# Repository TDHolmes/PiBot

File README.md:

# PiBot

MicroPython based robot designed for openness, flexibility, and education.

## Design
The PiBot is designed for simplicity, but also expandability. It is based on MicroPython at its core
and features simple to use pre-made APIs to interface with the hardware, allowing for easy design of
your robot.

## Hardware
The PiBot uses:
 - a mk20dx256vlh7 processor, just like the teensy 3.1 and 3.2
 - a MC33926PNB motor driver
 - pololu motors + encoders (for beta unit)

TESTING SHIT

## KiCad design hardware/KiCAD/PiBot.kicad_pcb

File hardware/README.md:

# Hardware
This folder will contain all PCB and schematic files written in KiCad

# Schematic Symbol Design Specs
* Name Text Size: 0.635mm
* Number Text Size: 0.635mm
* Length: 2.54mm

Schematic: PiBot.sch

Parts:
C1: 100uF; C_1210
C2, C7, C8: 10uF; C_1206
C3, C6: 1uF; C_0402
C4: 10nF; C_0402
C5: 0.1uF; C_0402
D1, D2, D4, D6: LED; PLCC2-LED-Reverse; Part Number XZVG45S-9
D3: Schottky; SOD-323; MPN CUS10S30H3FCT-ND
D5: 5.1V; SMA_Standard; Part Number SMAZ5V1-13-F
D7: 3.3V; SOD-323; Part Number MM3Z3V3ST1G
JP1, JP2: Jumper_NC_Small; Jumper-NC
JP3: Jumper_NO_Small; Jumper-NO
P2: CONN_02X05; Pin_Header_Straight_2x05_Pitch1.27mm
P3: I2C_EXPANSION; Pin_Header_Straight_2x01_Pitch2.54mm
P5: Feather-Adaper; feather-headers
PTC1: 0.5A; Fuse_SMD1206_Reflow; MPN 0ZCJ0050FF2G
R1: 150R; R_0402
R2, R6: 62R; R_0402
R3: 200R; R_0805
R4, R5, R7, R8, R10: 10k; R_0402
R9: 15k; R_0402
SD1: SD_CARD_SLOT_MICRO_RIGHT; MF_Connectors-MF-MICROSD
TP1, TP2, TP3, TP5, TP7, TP8, TP9, TP11, TP13, TP14, TP15, TP17, TP19, TP21, TP23, TP25, TP27, TP29, TP31, TP33, TP35, TP37, TP39, TP41, TP43, TP45, TP47, TP49: TEST; Measurement_Point_Round-SMD-Pad_Small
U1: DMG2302U; SOT-23
U2: MKL03ZxxVFK4; QFN-24_4x4mm_Pitch0.5mm

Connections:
+3V3: C1.1, C2.1, C3.1, C4.1, C5.1, C6.1, C7.1, JP2.1, P2.1, P5.27, R2.1, R4.1, R5.1, R6.1, R7.1, SD1.PIN4, TP1.1, U2.3; also elsewhere on the board
+5V: PTC1.1, R1.1, TP7.1; also elsewhere on the board
+BATT: R3.1, R9.2, TP13.1; also elsewhere on the board
/F_VBUS: D3.1, D5.1, P5.3
/I2C_LSB_BIT: JP2.2, JP3.2, U2.21
/VBATT_MONITOR: C8.1, D7.1, R9.1, R10.2, U2.16
FB_L: TP49.1, U2.15; also elsewhere on the board
FB_R: TP29.1, U2.12; also elsewhere on the board
GND: C1.2, C2.2, C3.2, C4.2, C5.2, C6.2, C7.2, C8.2, D1.1, D2.1, D4.1, D5.2, D7.2, JP3.1, P2.3, P2.5, P2.9, P5.13, P5.25, R8.1, R10.1, SD1.G0, SD1.G1, SD1.PIN6, TP2.1, TP8.1, TP14.1, U1.2, U2.4; also elsewhere on the board
MISO: P5.16, SD1.PIN7, TP33.1
MOSI: P5.17, SD1.PIN3, TP31.1
MotorL_Inv: TP45.1, U2.10; also elsewhere on the board
Motor_In1: TP9.1, U2.5; also elsewhere on the board
Motor_In2: TP11.1, U2.6; also elsewhere on the board
unnamed: D1.2, R1.2
unnamed: D2.2, R2.2
unnamed: D3.2, PTC1.2
unnamed: D4.2, R3.2
unnamed: D6.1, U1.3
unnamed: D6.2, R6.2
unnamed: JP1.1, P5.19
unnamed: SD1.PIN1, SD1.PIN9
PG: P5.2, TP3.1; also elsewhere on the board
RESET: P2.10, U2.23
SCK: P5.18, SD1.PIN5, TP27.1
SCL: P3.1, P5.11, R5.2, TP17.1, U2.17; also elsewhere on the board
SDA: P3.2, P5.12, R4.2, TP21.1, U2.18; also elsewhere on the board
SD_CS: JP1.2, R8.2, SD1.PIN2, TP37.1
SWCLK: P2.4, U2.22
SWDIO: P2.2, U2.24
SWO: P2.6, U2.19
front_bumper: TP47.1, U2.11; also elsewhere on the board
left_encA: TP35.1, U2.1; also elsewhere on the board
left_encB: TP39.1, U2.2; also elsewhere on the board
rear_bumper: TP43.1, U2.8; also elsewhere on the board
right_encA: TP15.1, U2.13; also elsewhere on the board
right_encB: TP19.1, U2.14; also elsewhere on the board
~MotorL_D: TP41.1, U2.9; also elsewhere on the board
~MotorR_D: TP23.1, U2.20; also elsewhere on the board
~MotorSF: TP5.1, U1.1, U2.7; also elsewhere on the board
~RST: P5.28, R7.2

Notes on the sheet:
PycoBot (Teensy uPython Robot)
By: Broderick Carlin Tyler Holmes
MIT License
5v Line Up
On Feather boards, VBUS connects directly to USB power. This is protection circuitry so we don’t blow our computers (or the feather circuitry).
Enable proc if our 5v line is up
5v line cannot be back-fed from proc.
Blinkies
Optionally, tie SD CS line low perminantly
3v3 Line Up
BATT Line Up
PTA5 - TPM0_CH1 SPI0_SS_b PTA6 - TPM0_CH0 SPI0_MISO PTB10 - TPM0_CH1 SPI0_SS_b PTB11 - TPM0_CH0 SPI0_MISO PTB5 - TPM1_CH1 CMP0_IN1 PTA12 - TPM1_CH0 TPM_CLKIN0
PWM Pins
Sensors
Power
*All LED's PN: XZVG45S-9
Motors
Debug + Expansion
SD Card
2.5:1 voltage divider
Motors OK
Test Points

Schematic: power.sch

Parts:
BT1, BT2, BT3, BT4: Battery; AA_Batt; Part Number BK-92
C9, C10, C13: 0.1uF; C_0402
C11, C12: 10uF; C_1206
C14: 10pf; C_0402
C15, C16, C17: 22uf; R_0402
D8, D9: 5.1V; SMA_Standard; Part Number SMAZ5V1-13-F
D10: 7.5V; SOD-323; Part Number DZ2J075M0L
JP4, JP18: Jumper_NO_Small; Jumper-NO
JP17: Jumper_NC_Small; NetTie-I_Connected_SMD
L1: 1 uH; Neosid_Inductor_SM-NE29_SMD1008; Part Number SRN2512-1R0M
R11, R12, R16: 0; R_0805
R13, R14: 1M; R_0402
R15: 111k; R_0402
R32: 10k; R_0402
SW1: SPST; JS202011SCQN; Part Number JS202011SCQN
U3, U17: N-FET; SOT-23; Part Number DMG2302U
U4: TPS63060; DFN-10-w_pad

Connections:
+5V: R16.2; also elsewhere on the board
+BATT: C11.1, C12.1, R11.2, U4.2, U4.3; also elsewhere on the board
/power/BATT_GND_TERM: BT4.2, D9.1, JP18.1, R32.2, U17.2
/power/BATT_V+_TERM: BT1.1, C9.1, C10.1, D8.1, D10.1, R11.1, SW1.2, U3.1
/power/PSU_FB: C14.1, R14.2, R15.1, U4.8
/power/PSU_IND: L1.1, U4.1
/power/PSU_VOUT: C15.1, C16.1, C17.1, R13.1, R14.1, R16.1, U4.9
GND: C10.2, C11.2, C12.2, C13.2, C14.2, C15.2, C16.2, C17.2, D10.2, JP4.2, JP17.1, R15.2, U3.2, U4.4, U4.7, U4.PAD; also elsewhere on the board
GNDPWR: JP17.2; also elsewhere on the board
unnamed: BT1.2, BT2.1
unnamed: BT2.2, BT3.1
unnamed: BT3.2, BT4.1
unnamed: C9.2, JP4.1, JP18.2, U3.3, U17.3
unnamed: C13.1, U4.6
unnamed: D8.2, D9.2
unnamed: L1.2, U4.10
unnamed: R12.2, R13.2, U4.5
unnamed: R32.1, SW1.1, U17.1
PG: R12.1; also elsewhere on the board

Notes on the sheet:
PycoBot (Teensy uPython Robot)
By: Broderick Carlin Tyler Holmes
MIT License

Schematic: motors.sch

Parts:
C18, C19, C22, C23, C24, C25, C26, C27, C28, C29, C30, C31: 0.1uF; C_0402
C20, C21, C32, C33: 1uF; C_0402
C34, C35: 10uF; C_1206
D11, D12: 3.3V; SOD-323; Part Number MM3Z3V3ST1G
JP5, JP6, JP11, JP12, JP13, JP14: Jumper_NC_Small; Jumper-NC
JP7, JP8, JP9, JP10: Jumper_NO_Small; Jumper-NO
R17, R18: 200; R_0805
R19, R20: 100; R_0402
R21, R22, R23, R24, R25, R26, R27: 10k; R_0402
U5, U6: MC33926PNB; PQFN-32-EP-0.8mm
U7, U8: Motor; Sanyo_GearMotor
U9, U10, U11, U12: AH3772; SOT-23

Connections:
+3V3: C24.1, C25.1, C26.1, C27.1, C30.1, C31.1, R23.1, R24.1, R25.1, R26.1, R27.1, U7.3, U8.3, U9.1, U10.1, U11.1, U12.1; also elsewhere on the board
+BATT: C18.1, C19.1, C28.1, C29.1, C32.1, C33.1, C34.1, C35.1, U5.4, U5.6, U5.11, U5.31, U6.4, U6.6, U6.11, U6.31; also elsewhere on the board
FB_L: JP5.1; also elsewhere on the board
FB_R: JP6.1; also elsewhere on the board
GND: C20.2, C21.2, C24.2, C25.2, C26.2, C27.2, C30.2, C31.2, D11.2, D12.2, R17.2, R18.2, R21.2, R22.2, U5.5, U5.pad, U6.5, U6.pad, U7.6, U8.6, U9.2, U10.2, U11.2, U12.2; also elsewhere on the board
GNDPWR: C28.2, C29.2, C32.2, C33.2, C34.2, C35.2, U5.18, U5.19, U5.20, U5.22, U5.23, U5.24, U6.18, U6.19, U6.20, U6.22, U6.23, U6.24; also elsewhere on the board
MotorL_Inv: U5.7; also elsewhere on the board
Motor_In1: U5.2, U6.2; also elsewhere on the board
Motor_In2: U5.1, U6.1; also elsewhere on the board
unnamed: C18.2, U6.32
unnamed: C19.2, U5.32
unnamed: C20.1, D11.1, JP5.2, R17.1, R19.2
unnamed: C21.1, D12.1, JP6.2, R18.1, R20.2
unnamed: C22.1, U5.12, U5.13, U5.14, U5.15, U7.1
unnamed: C22.2, U5.27, U5.28, U5.29, U5.30, U7.2
unnamed: C23.1, U6.12, U6.13, U6.14, U6.15, U8.1
unnamed: C23.2, U6.27, U6.28, U6.29, U6.30, U8.2
unnamed: JP7.1, U7.4
unnamed: JP8.2, U7.5
unnamed: JP9.1, U8.4
unnamed: JP10.2, U8.5
unnamed: JP11.1, R23.2, U9.3
unnamed: JP12.1, R25.2, U10.3
unnamed: JP13.1, R26.2, U11.3
unnamed: JP14.1, R27.2, U12.3
unnamed: R19.1, U5.8
unnamed: R20.1, U6.8
unnamed: R21.1, U5.26
unnamed: R22.1, U6.26
PG: U5.10, U6.10; also elsewhere on the board
left_encA: JP7.2, JP13.2; also elsewhere on the board
left_encB: JP8.1, JP11.2; also elsewhere on the board
right_encA: JP9.2, JP14.2; also elsewhere on the board
right_encB: JP10.1, JP12.2; also elsewhere on the board
~MotorL_D: U5.16; also elsewhere on the board
~MotorR_D: U6.16; also elsewhere on the board
~MotorSF: R24.2, U5.21, U6.21; also elsewhere on the board

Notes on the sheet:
FB_L/R are feedback analog lines for sensing the amount of current the motor driver is sending. The voltage measured on this line divided by 0.48ohm will give the motor current
Enable Motor Drivers if our 5v line is up
Magnetic Motor Encoders
Right Motor
Left Motor
Common Components
By: Broderick Carlin Tyler Holmes
MIT License
PycoBot (Teensy uPython Robot)

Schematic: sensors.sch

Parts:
C36, C37, C38, C39, C43, C47: 0.1uF; C_0402
C40, C45: 10uF; C_1206
C41: 10nF; C_0402
C42, C46: 1uF; C_0402
C44: 4.7uF; R_0402
C48: 0.22uF; R_0402
DRDY1: TEST; Measurement_Point_Round-SMD-Pad_Small
INT1, INT2: TEST; Measurement_Point_Round-SMD-Pad_Small
JP15: Jumper_NC_Small; Jumper-NC
JP16: Jumper_NO_Small; Jumper-NO
R28, R29, R30, R31: 10k; R_0402
SW2, SW3, SW4, SW5: SW_SPDT; TS0101F020V3; Part Number TS0101F020V3
TP4, TP6, TP10, TP12: TEST; Measurement_Point_Round-SMD-Pad_Small
U13, U14: BH1745NUC; DFN-8_2x2mm_Pitch0.5mm
U15: L3GD20H; 16-LGA-3x3
U16: LSM303DLHCTR; 14-LGA-3x5

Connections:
+3V3: C36.1, C37.1, C40.1, C42.1, C43.1, C45.1, C46.1, C47.1, JP15.2, SW2.3, SW3.3, SW4.3, SW5.3, U13.1, U13.2, U14.2, U15.1, U15.5, U15.16, U16.1, U16.14; also elsewhere on the board
GND: C36.2, C37.2, C38.2, C39.2, C40.2, C41.2, C42.2, C43.2, C44.2, C45.2, C46.2, C47.2, JP16.1, R30.1, R31.1, U13.3, U13.4, U14.1, U14.3, U14.4, U15.8, U15.9, U15.10, U15.11, U15.12, U15.13, U15.15, U16.7, U16.10, U16.11; also elsewhere on the board
unnamed: C41.1, U15.14
unnamed: C44.1, U16.6
unnamed: C48.1, U16.13
unnamed: C48.2, U16.12
unnamed: DRDY1.1, U16.9
unnamed: INT1.1, U16.5
unnamed: INT2.1, U16.4
unnamed: JP15.1, JP16.2, U15.4
unnamed: R28.1, R30.2, SW2.2, SW3.2
unnamed: R29.1, R31.2, SW4.2, SW5.2
unnamed: TP4.1, U13.7
unnamed: TP6.1, U14.7
unnamed: TP10.1, U15.7
unnamed: TP12.1, U15.6
SCL: U13.5, U14.5, U15.2, U16.2; also elsewhere on the board
SDA: U13.6, U14.6, U15.3, U16.3; also elsewhere on the board
front_bumper: C39.1, R29.2; also elsewhere on the board
rear_bumper: C38.1, R28.2; also elsewhere on the board

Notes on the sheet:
Gyroscope
Accelerometer Magnetometer
Color Sensors
Bumpers
addr: 0x32
addr: 0x3C
addr: 0xD6 (alt 0xD4)
addr: 0x70 0x72
By: Broderick Carlin Tyler Holmes
MIT License
PycoBot (Teensy uPython Robot)
rear left
rear right
front left
front right
Per datasheet, connect reserved pins to GND.

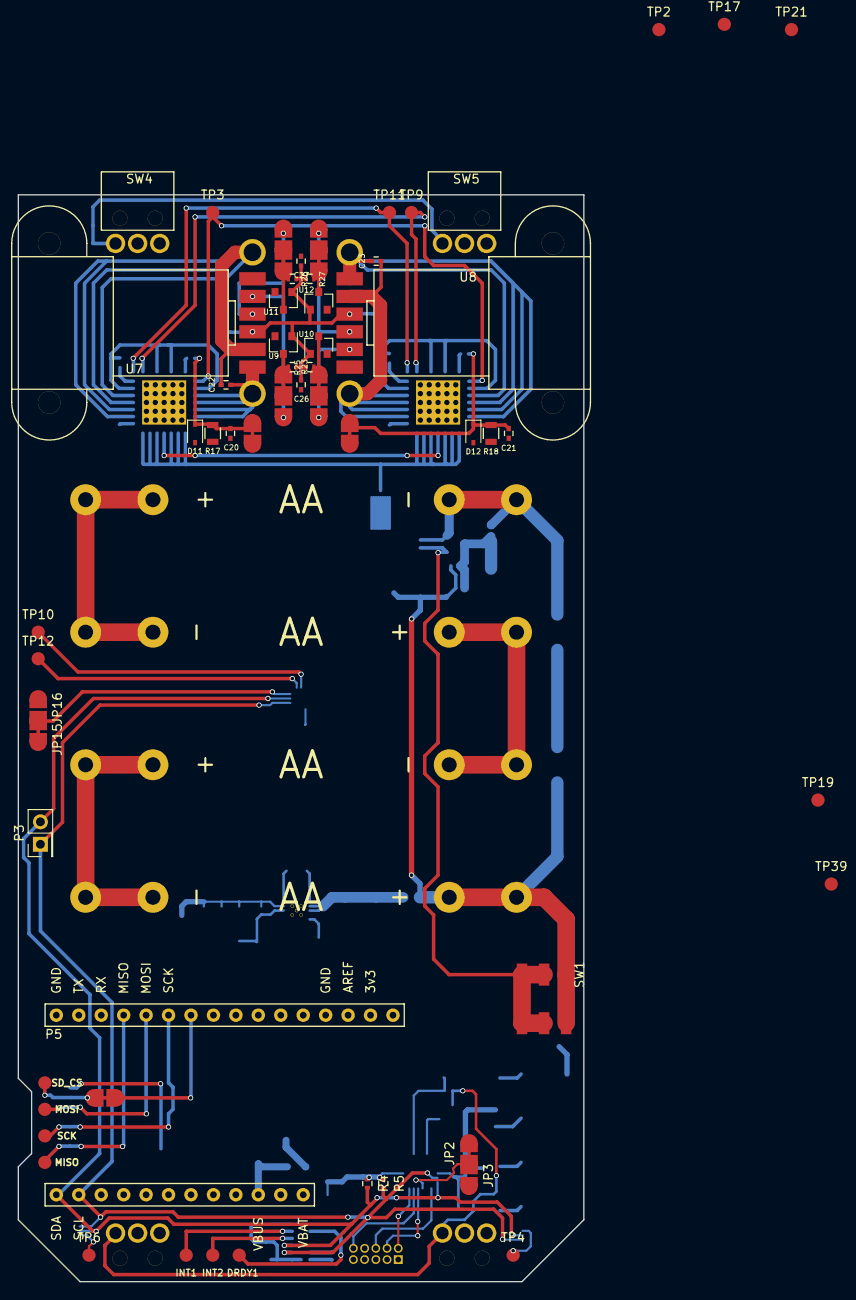
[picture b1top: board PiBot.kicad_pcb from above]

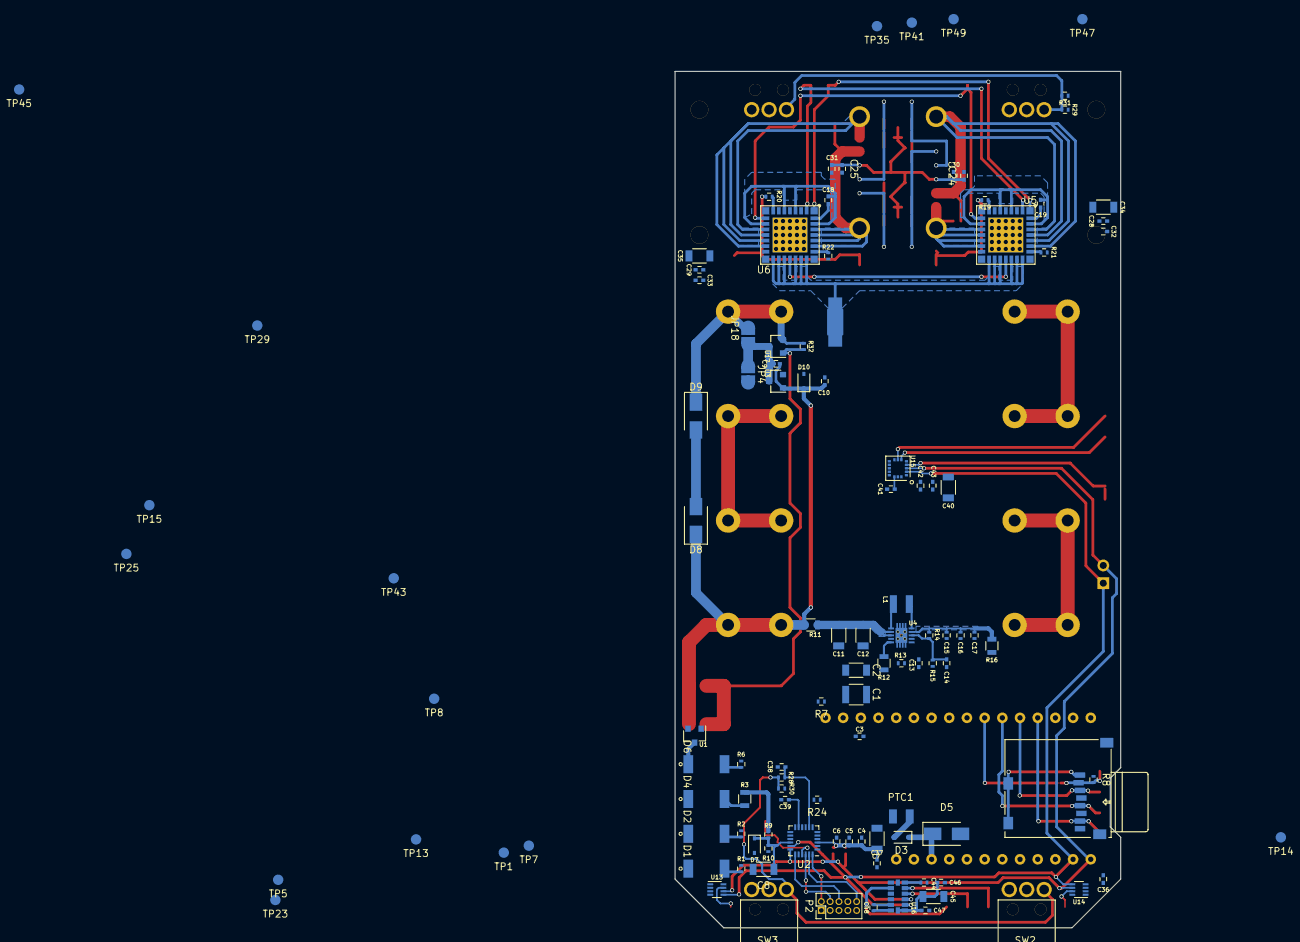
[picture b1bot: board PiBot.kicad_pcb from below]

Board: 2 copper layers, 64.0 x 123.0 mm, 177 parts (112 on the bottom side), 90 nets.

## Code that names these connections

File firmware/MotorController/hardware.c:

/*
* Copyright (c) 2015, Freescale Semiconductor, Inc.
* All rights reserved.
*
* Redistribution and use in source and binary forms, with or without modification,
* are permitted provided that the following conditions are met:
*
* o Redistributions of source code must retain the above copyright notice, this list
*   of conditions and the following disclaimer.
*
* o Redistributions in binary form must reproduce the above copyright notice, this
*   list of conditions and the following disclaimer in the documentation and/or
*   other materials provided with the distribution.
*
* o Neither the name of Freescale Semiconductor, Inc. nor the names of its
*   contributors may be used to endorse or promote products derived from this
*   software without specific prior written permission.
*
* THIS SOFTWARE IS PROVIDED BY THE COPYRIGHT HOLDERS AND CONTRIBUTORS "AS IS" AND
* ANY EXPRESS OR IMPLIED WARRANTIES, INCLUDING, BUT NOT LIMITED TO, THE IMPLIED
* WARRANTIES OF MERCHANTABILITY AND FITNESS FOR A PARTICULAR PURPOSE ARE
* DISCLAIMED. IN NO EVENT SHALL THE COPYRIGHT HOLDER OR CONTRIBUTORS BE LIABLE FOR
* ANY DIRECT, INDIRECT, INCIDENTAL, SPECIAL, EXEMPLARY, OR CONSEQUENTIAL DAMAGES
* (INCLUDING, BUT NOT LIMITED TO, PROCUREMENT OF SUBSTITUTE GOODS OR SERVICES;
* LOSS OF USE, DATA, OR PROFITS; OR BUSINESS INTERRUPTION) HOWEVER CAUSED AND ON
* ANY THEORY OF LIABILITY, WHETHER IN CONTRACT, STRICT LIABILITY, OR TORT
* (INCLUDING NEGLIGENCE OR OTHERWISE) ARISING IN ANY WAY OUT OF THE USE OF THIS
* SOFTWARE, EVEN IF ADVISED OF THE POSSIBILITY OF SUCH DAMAGE.
*/

#include "hardware.h"
#include "fsl_port.h"


/*******************************************************************************
 * Variables
 ******************************************************************************/

/*******************************************************************************
 * Code
 ******************************************************************************/

/* initialize GPIO pins and setup hardware modules */
void hw_init_pins(void)
{
    /* Ungate the port clock */
    CLOCK_EnableClock(kCLOCK_PortA);
    CLOCK_EnableClock(kCLOCK_PortB);
    // Setup PORTB
    PORT_SetPinMux(PORTB, 0u, kPORT_PinDisabledOrAnalog); // FB_R - Analog read of the right motor (ADC0_SE9 by default)
    PORT_SetPinMux(PORTB, 1u, kPORT_MuxAsGpio);           // right_encA - Digital square wave to read encoder distance... (alt 1)
    PORT_SetPinMux(PORTB, 2u, kPORT_MuxAsGpio);           // right_encB - Digital square wave to read encoder distance... (alt 1)
    PORT_SetPinMux(PORTB, 3u, kPORT_MuxAlt2);             // I2C_SCL - I2C Clock (alt 2)
    PORT_SetPinMux(PORTB, 4u, kPORT_MuxAlt2);             // I2C_SDA - I2C Data (alt 2)
    // JTAG_SWO - JTAG SWO pin (N/A)
    PORT_SetPinMux(PORTB, 6u, kPORT_MuxAsGpio);           // left_encA - Digital square wave to read encoder distance... (alt 1)
    PORT_SetPinMux(PORTB, 7u, kPORT_MuxAsGpio);           // left_encB - Digital square wave to read encoder distance... (alt 1)
    PORT_SetPinMux(PORTB, 10u, kPORT_MuxAlt2);            // MotorL_D_n - Disables the left motor. Can PWM for speed control (TPM0_CH1 - alt 2)
    PORT_SetPinMux(PORTB, 11u, kPORT_MuxAsGpio);          // MotorL_Inv - Invert the left motors direction (alt 1)
    PORT_SetPinMux(PORTB, 13u, kPORT_MuxAsGpio);          // I2C_LSB_BIT - Controls the I2C address least significant bit (alt 1)

    // JTAG_SWCLK - JTAG SWCLK pin (N/A)
    // JTAG_RESET - JTAG RESET pin (N/A)
    // JTAG_SWDIO - JTAG SWDIO pin (N/A)
    PORT_SetPinMux(PORTA, 3u, kPORT_MuxAlt4);             // rear_bumper - rear bumper sensor   (alt 1) / Debug UART-TX (alt 4)
    PORT_SetPinMux(PORTA, 4u, kPORT_MuxAlt4);             // front_bumper - front bumper sensor (alt 1) / Debug UART-RX (alt 4)
    PORT_SetPinMux(PORTA, 5u, kPORT_MuxAsGpio);           // MotorSF_n - Motor status flag to indicate a motor driver error (alt 1)
    PORT_SetPinMux(PORTA, 6u, kPORT_MuxAsGpio);           // Motor_In1 - Motor driver input (alt 1)
    PORT_SetPinMux(PORTA, 7u, kPORT_MuxAsGpio);           // Motor_In2 - Motor driver input (alt 1)
    PORT_SetPinMux(PORTA, 8u, kPORT_PinDisabledOrAnalog); // FB_L - Analog read of the left motor (ADC0_SE3 by default)
    PORT_SetPinMux(PORTA, 9u, kPORT_PinDisabledOrAnalog); // VBATT_MONITOR - Analog read of the motor voltage. (ADC0_SE2 by default)
    PORT_SetPinMux(PORTA, 12u, kPORT_MuxAlt2);            // MotorR_D_n - Disables the right motor. Can PWM for speed control (TPM1_CH0 = alt 2)
}

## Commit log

2016-11-16 adding some text to the REDME
2016-11-16 Fixing bullet list.
2016-11-16 adding organizational folders
2016-11-17 initial creation of the processor
2016-11-18 adding power updates
2016-11-18 stupid lib gitignore
2016-11-19 Added Motor Driver and Cleanup
    Added motor driver chip to PiBot KiCad library and also clean up repo adding files to gitignore that are not crucial to the project
2016-11-19 Fix README
    Rename the readme file in hardware folder to comply with github standards. Also added specs for creating schematic symbols
2016-11-21 Added Motor and Encoder shematic
    Also added preliminary wiring and change grounds to better illustrate what the grounds were used for
2016-11-21 Add missing documentation and fix filenames
2016-11-22 adding in PQFN package for motor driver
2016-11-22 moving the micro to the PiBot lib
2016-11-22 adding in color sensors
2016-11-22 Added Mag schematic diagram and added to schematic
2016-11-22 Added Molex Micro SD card schematic symbol
2016-11-23 adding BH1745NUC instead of the original plan for the TCS34725FNCT
2016-11-24 adding in feather header adapter
2016-11-24 wired up the header
2016-11-24 added USB connection
2016-11-24 Fix problems after merge and move overlapping parts
2016-11-24 Fix overlapping parts
2016-11-24 adding SPI pinout to SD card
2016-11-24 renamed footprint library to PiBot and made minor adjustments to the schematic
2016-11-24 added WSON008X2120 package for color sensor
2016-11-27 adding micropython as a submodule
2016-11-27 adding in teensy uPython required LED. Should add more (power and such)
2016-11-28 Relocate SD card
2016-12-19 Add in battery, reverse voltage protection, and 5V regulator
2016-12-19 Connect power ground at battery
2016-12-19 Add extra protection circuitry and 0ohm NP
2016-12-19 Add 0 ohm's to power rails
    This way we can isolate power rails for initial powerup and isolate entire rails
2016-12-19 Removed processor, modified feather headers, added USB protection
2016-12-19 Revert "Removed processor, modified feather headers, added USB protection"
    This reverts commit 60d192fd1a22e075bf83db74977d7e75c925eb56.
2016-12-19 Merging power changes
    KiCad + git = </3
2016-12-20 more wiring up
2016-12-23 Added enable logic to Feather board and motor drivers to ensure they only enable if battery is up.
2016-12-24 Added net labels, misc reformatting...
2016-12-24 Fixed motor pinout
2016-12-26 Fix parts that were not defined
2016-12-26 Cleanup
    Reorg of some lines, cleaning everything up to make it all pretty again
2016-12-26 Fix 5v psu isolation
    Add an additional 0ohm to isolate the 'power good' line so that weirdness doesn't occur whent he 5v line is cut off
2016-12-27 fixing up some nit picky things
2016-12-27 adding in MKL03Z files
2016-12-28 tweaking build scripts for the hello_world demo to be used in the main project
2016-12-29 Moving some files to the top level of the MotorController/MKL03Z folder to start development.
2016-12-29 ignore the CMakeFiles folder
2016-12-29 adding in I2C slav
2016-12-29 removing CMakeFiles directory from the git repo
2016-12-30 changing build system to using a python file instead of shell scripts
2016-12-30 tweaking the build script
2016-12-31 Add micro and JTAG
    Added micro schematic symbol and wired up to power and JTAG using the defined 10-pin ARM jtag standard
2017-01-01 more firmwareeeee
2017-01-01 hooked up KL03 micro and refactored power to a new sheet
2017-01-01 update schematic symbols that were out of date
2017-01-01 Modify build script to allow for custom build install
    User can specify where the gcc compiler is to support the install of multiple armgcc compilers
2017-01-01 fixing whitespace issue
2017-01-03 getting rid of one folder level in MotorController coprocessor and added a README
2017-01-03 removing all of the HTML documentation because it exists in PDF form
2017-01-03 adding in files for handling the encoders
2017-01-03 remove old mag and add accel, mag, gyro
2017-01-03 Add bumpers, user LED, and hall sensors
2017-01-03 added in source to support encoders and the motor drivers
2017-01-03 Organize schematic into multiple sheets
2017-01-03 Fix Library dependancies
2017-01-03 Remove user LED and add battery monitor
    user LED was sacraficed to make room for battery voltage monitor circuit
2017-01-03 add missing documentation
2017-01-04 Replace mag/accel and add addresses
    Replace the mag/accel chip with one that is in stock and add all i2c device addresses as notes for reference
2017-01-04 Fix errors in schematic
    - Fix motor feedback circuit
    - Replace micro SD card with standard symbol
    - Replace some 0ohm's with cuttable traces
    - Clean up motor sheet
2017-01-04 Minor cleanup
2017-01-04 Fix some errors and add test point
    Fixed errors with motor pinout and add test points
2017-01-05 Minor cleanup; added breakouts for some things
2017-01-05 Split battery into 4 individual batteries
2017-01-05 Remove all references to rescue library
2017-01-05 Remove rescue library from actual project file
2017-01-05 Move SD CS line off of UART RX line
2017-01-05 Clean up a couple resistor labels
2017-01-05 Start matching schematic symbols with footprints
2017-01-05 Add MacroFab library and update SD card
2017-01-06 adding in PQFN to motor controller
2017-01-06 Add LGA layouts for sensors
2017-01-06 Add battery footprint and assign feather footrprint
2017-01-06 fixing up PQFN
2017-01-06 Add the rest of the missing footprints, aside from motor
2017-01-06 Remove random PDF's that were accidentally added
2017-01-07 Started board layout
2017-01-07 Dry positioning of large portion of the components
2017-01-08 Initial laying of traces, still work to get done
    batt_v+_term trace is way too thing right now
2017-01-08 Wire up motor drive power
2017-01-09 Motor drives wired up
2017-01-09 pulling micropython and switching to master
2017-01-09 fixing GND_PWR connection
2017-01-09 Revert "fixing GND_PWR connection" because it is not compatible with the current stable version of KiCad
    This reverts commit 5be297efdf6c88a46329cd071e672a911a750ef8.
2017-01-09 Inital routing done!!!!!
2017-01-17 First cut at slave comms
2017-01-17 adding .DS_store to .gitignore
2017-01-22 renaming main
2017-01-22 adding in a timer module
2017-01-22 cleaning up I2C stuff
2017-01-22 removing unnecessary file
2017-01-22 refactoring motor_calc and adding PID functions
2017-01-22 refactoring motor_drivers for more clarity
2017-01-22 misc cleaning up and removing unnecessary functions
2017-01-23 working on getting to compileable code
2017-02-05 added clang compilation support
2017-02-05 adding some PID functions
2017-02-05 fixing logical and to bitwise and
2017-02-05 adding PID target set and completion checks
2017-02-05 modifying startup assembly to be compatible with clang compiler
2017-02-05 removing apparently unused pin_mux.h
2017-02-05 switchin from janky casting to union
2017-02-05 cleanup
2017-02-13 adding switches around memory mapped definitions to allow for potential host side unit tests
2017-02-13 putting constants into a unified location to avoid unnecessary dependencies
2017-02-13 adding gcc cmake file for potential use for host side unit testing
2017-02-13 slight changes to build script
2017-02-13 adding volatile keyword to preserve volatile behavior in counter variable
2017-02-13 reducing unnecessary includes and getting rid of an unnecessary warning
2017-02-13 cleaning up dependencies
2017-02-13 adding in unit tests
2017-02-13 adding more flexible unit test parameters
2017-02-13 adding ifdefined check around min and max macros to avoid compiler warning
2017-02-13 refactor to avoid INF and reduce dependencies
2017-02-13 fixing I2C slave config struct
2017-02-13 removing useless file
2017-02-13 adding verbose output option and more unit tests
2017-02-13 adding travis CI yml file
2017-02-13 removing micropython from my repo
2017-02-13 adding an ls -la command to figure out what is going wrong
2017-02-13 trying to clone unity during travis CI
2017-02-13 Fix the git crap
2017-02-13 changing my email address
2017-02-13 Edit readme to reflect build status
2017-02-13 Fixed gross formatting in readme
2017-02-13 Purposfully failing unit test
2017-02-13 fixing the failing test
2017-02-13 testing
2017-02-13 Makin shit pretty
2017-02-13 I clearly suck at this readme formatting
2017-02-13 Add Codacity badge
2017-02-13 making sure we don't use motor_calc_PID_is_done incorrectly
2017-02-13 Fix dumb badge
2017-02-13 Add license badge cause badges apparently make the code better
2017-02-16 adding a .clang_complete file for atom text edit clang linting
2017-02-19 reducing inter-dependency
2017-02-19 switching over to not having a function in main to be called by utility files
2017-02-19 adding in Debug stuff back in to compile
2017-02-19 updating .clang_complete for atom clang linting
2017-02-19 fixing unit tests due to adding MM_PER_ENCODER_TICK multiplication
2017-02-20 Start of relayout
2017-02-21 MANY CHANGES
2017-02-23 Adding proper pin config in hw setup
2017-02-23 removing dummy_test from unit test runner
2017-03-11 whitespace change
2017-03-11 initial commit of ADC. Not much going on yet
2017-04-04 Headway on schematic layout
2017-04-06 Lay out encoders and begin motor drive
2017-04-11 Lay out motor drivers
2017-04-11 Layout PSU
2017-04-12 Finish part placement
    Now just to route everything :P
2017-04-14 More routing
2017-06-20 ignore build directories
2017-06-20 add some pictures

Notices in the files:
README.md:
License: MIT
